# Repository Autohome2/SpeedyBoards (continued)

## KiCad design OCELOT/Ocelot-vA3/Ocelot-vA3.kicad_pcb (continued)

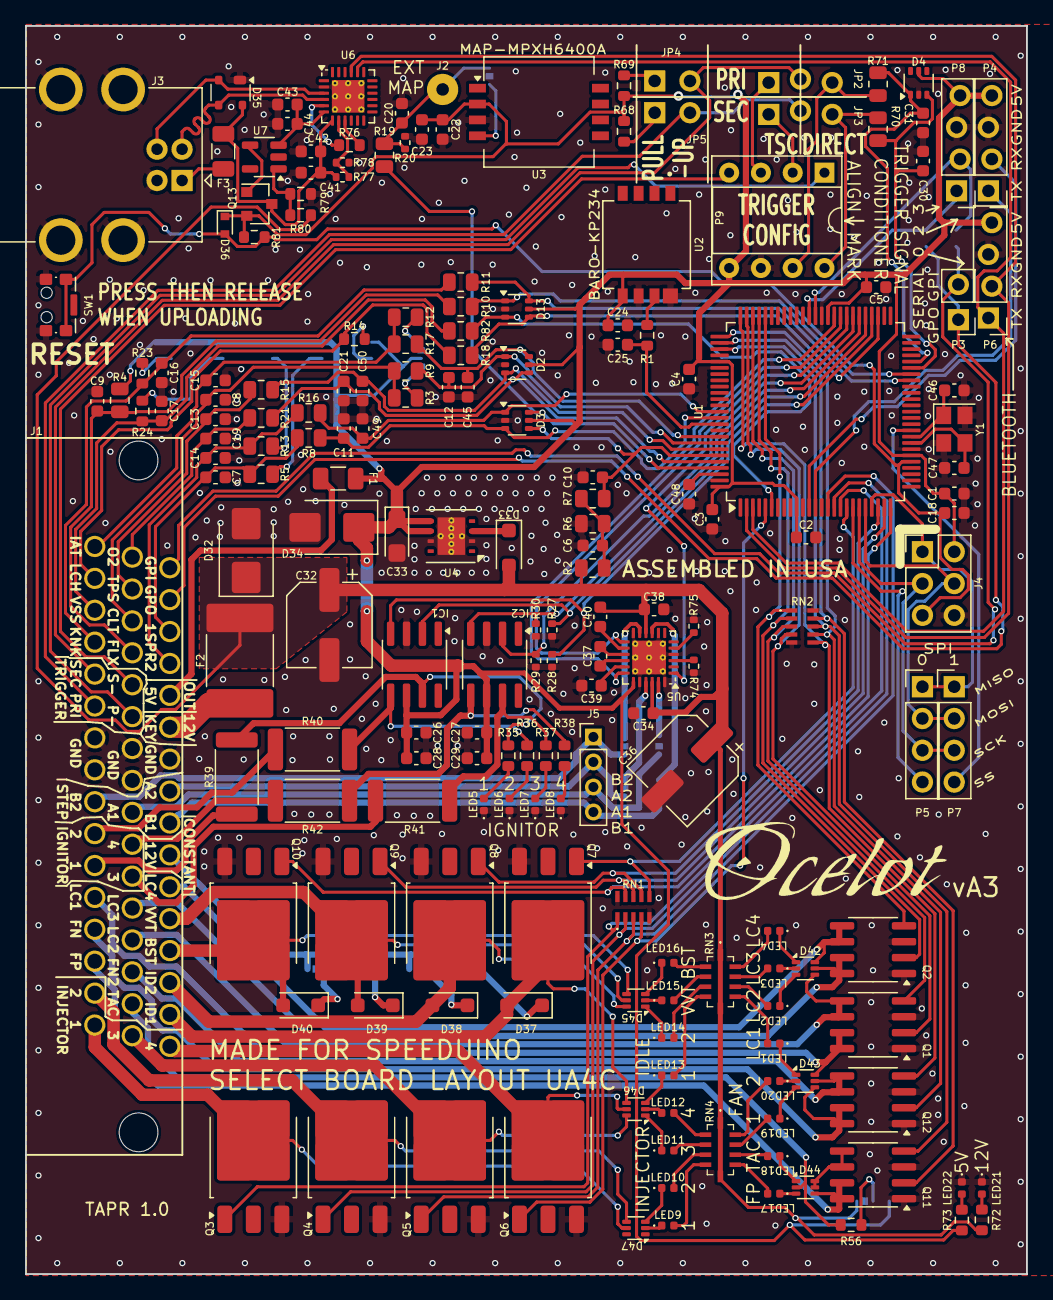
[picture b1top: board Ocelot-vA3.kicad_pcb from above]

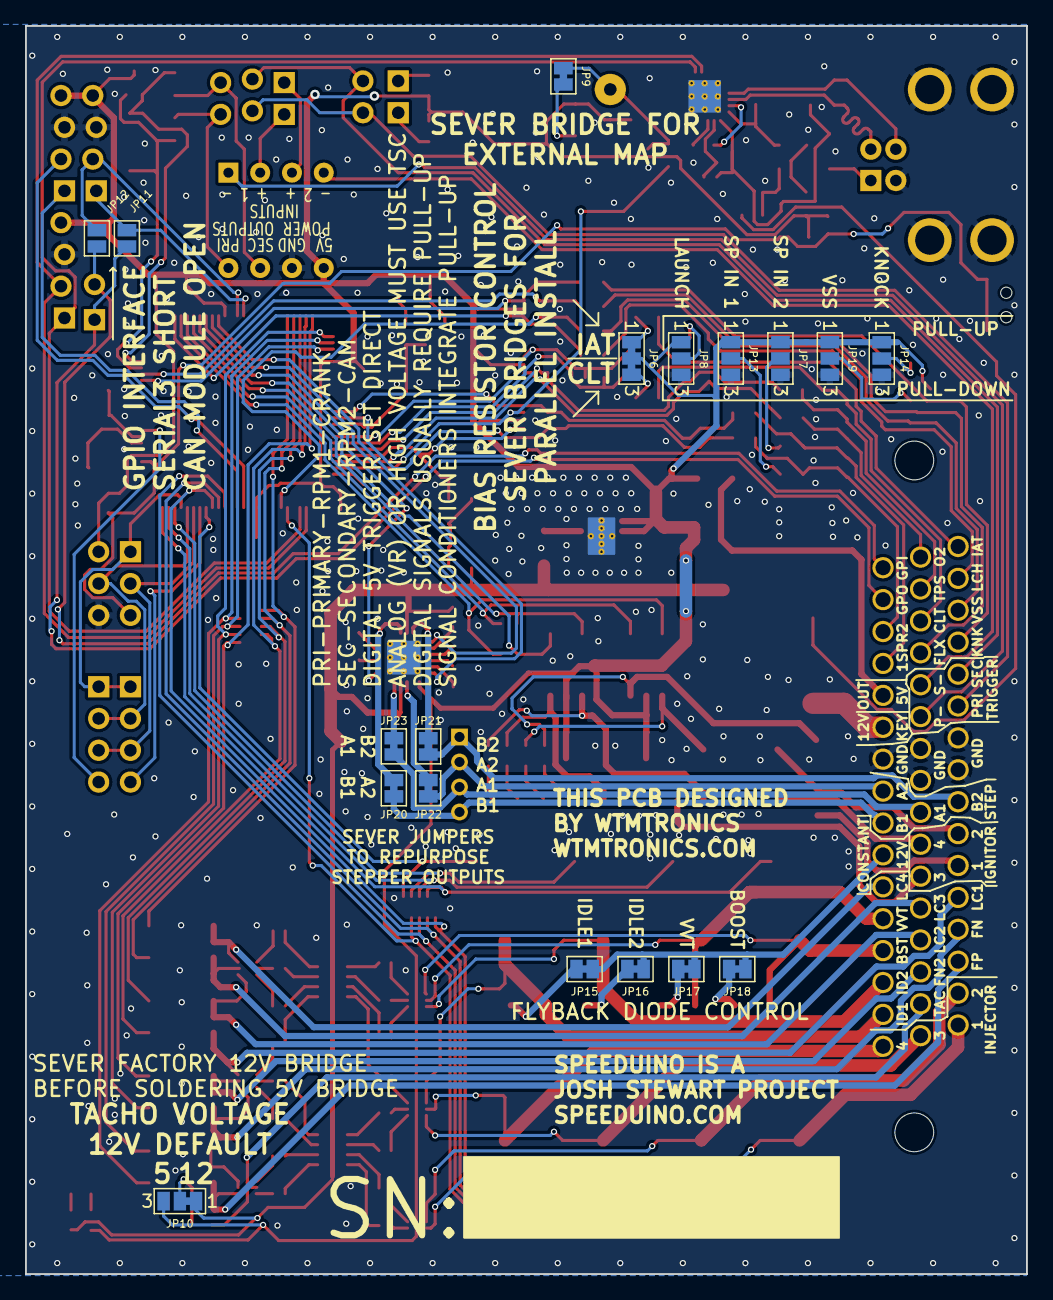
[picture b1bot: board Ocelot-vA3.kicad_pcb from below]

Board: 2 copper layers, 80.0 x 99.8 mm, 206 parts (18 on the bottom side), 185 nets.

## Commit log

2025-10-13 Update README.md
    Update for Ocelot A4
2025-10-13 Add Ocelot Design Files
    Add files for Ocelot A3 and A4
2025-10-13 Remove duplicates
